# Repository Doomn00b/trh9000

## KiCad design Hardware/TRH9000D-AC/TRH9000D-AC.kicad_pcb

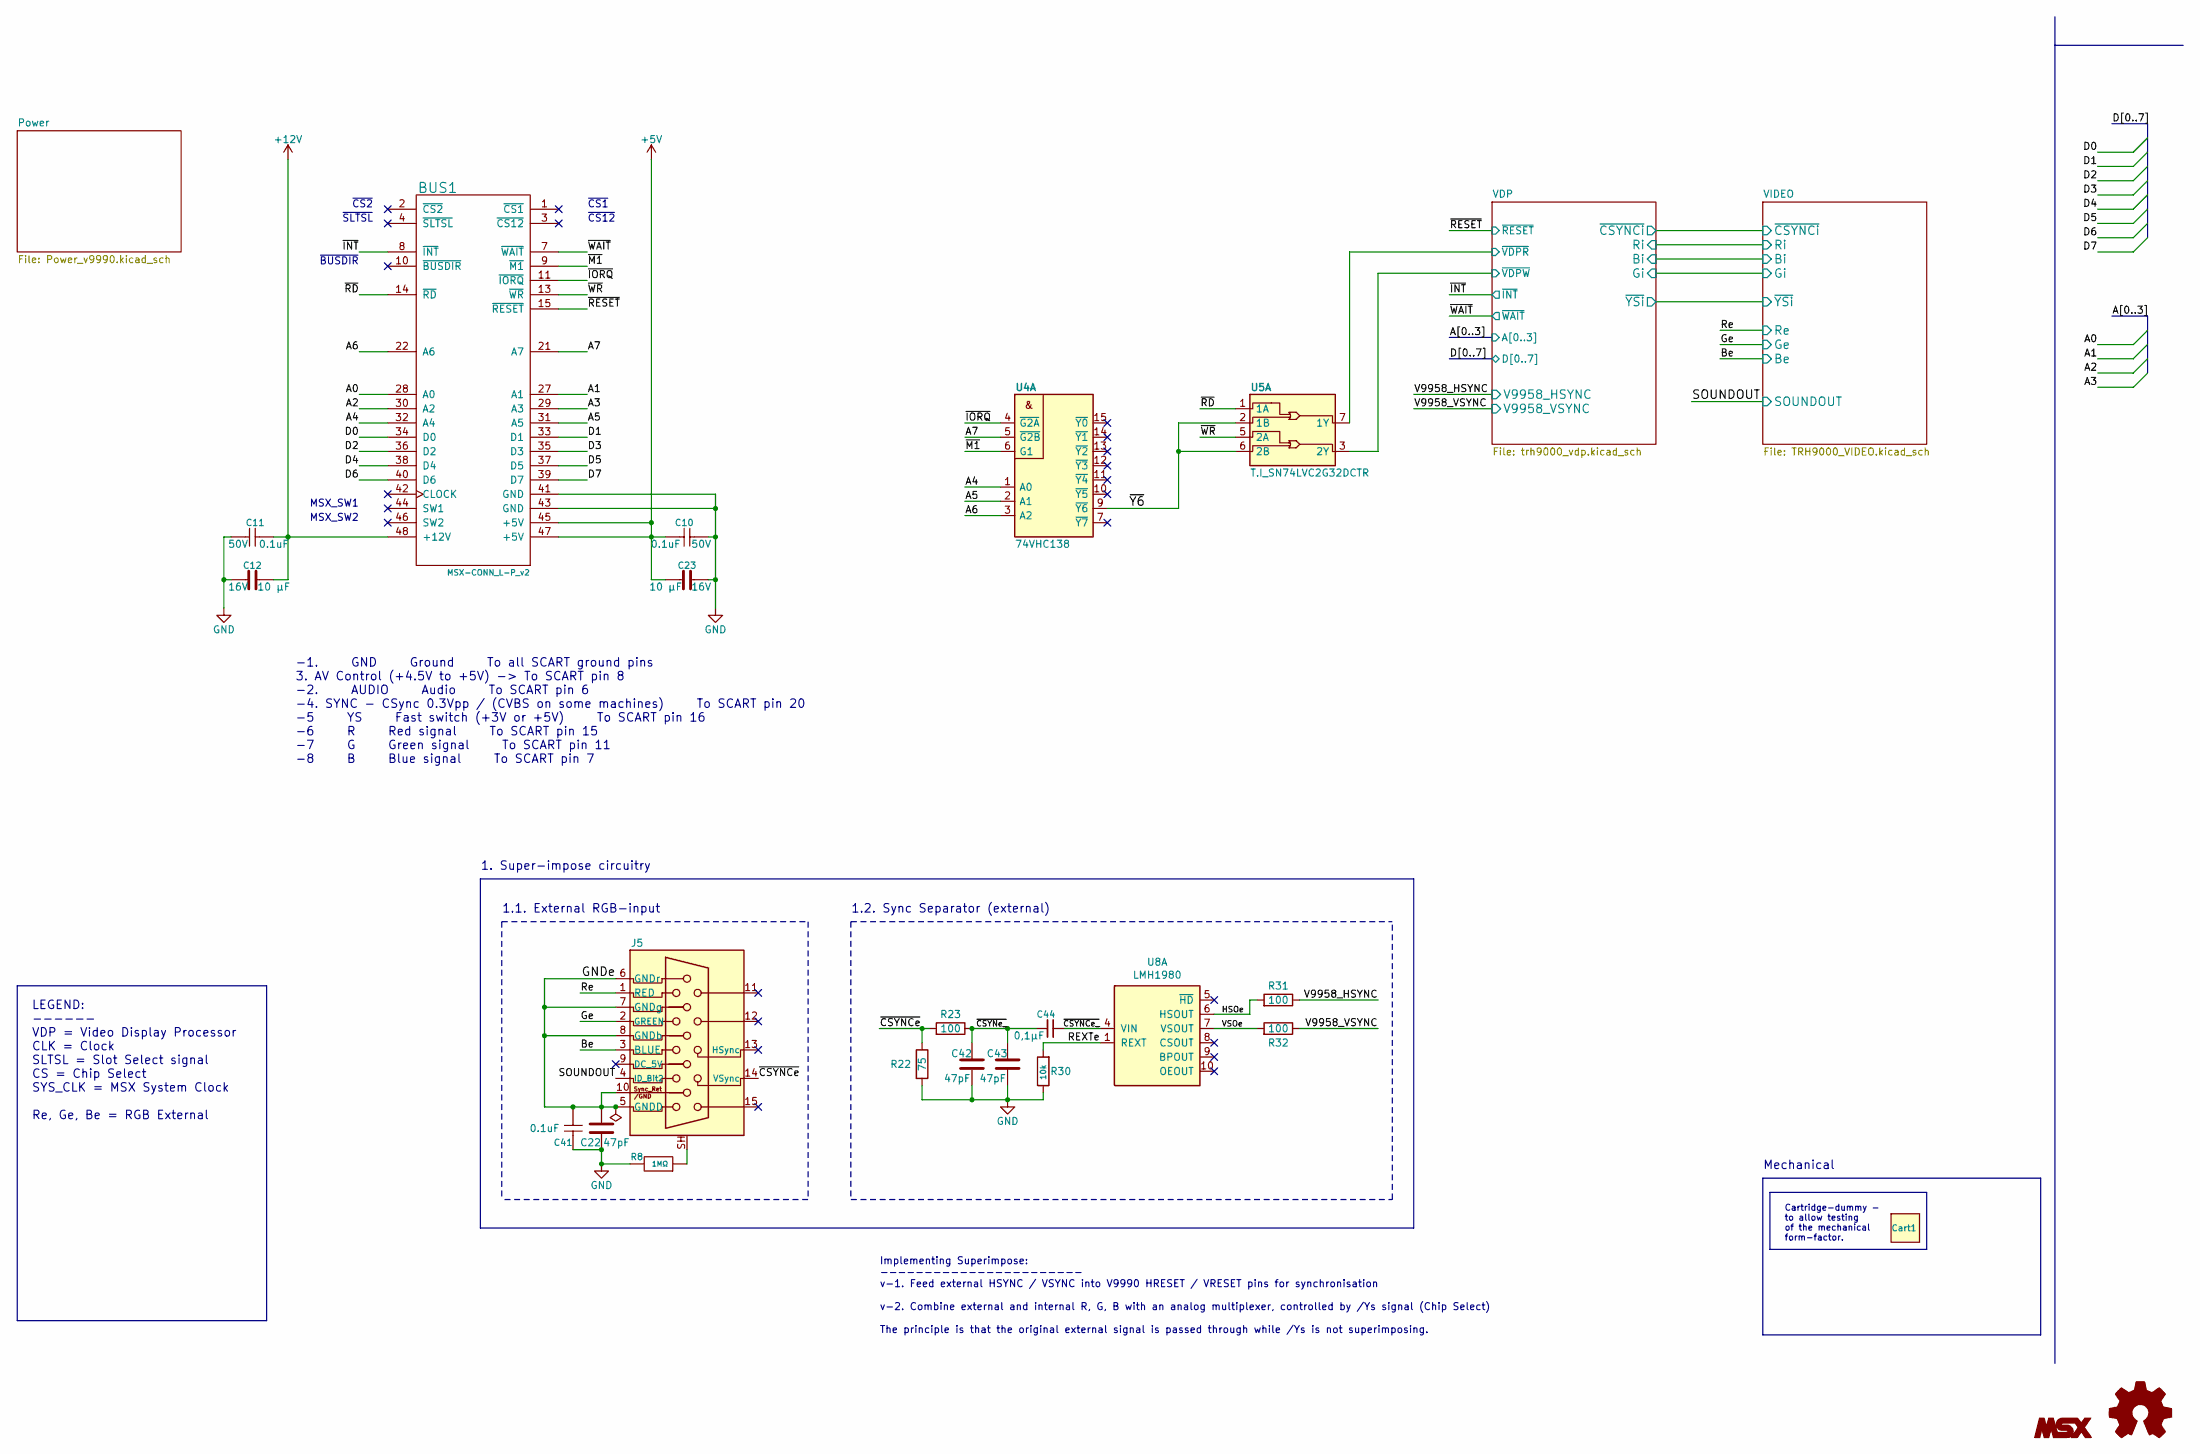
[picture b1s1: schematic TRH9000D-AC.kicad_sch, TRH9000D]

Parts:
BUS1: MSX-CONN_L-P_v2; msx_edge-conn-LP_v2; MPN n/a
C10, C11, C41: C_CC0805JPX7R9BB104; C_0805_2012Metric; Voltage rating 50V; MPN CC0805JPX7R9BB104
C12, C23: C_CL21B106KOQNNNE; C_0805_2012Metric; Voltage rating 16V; MPN CL21B106KOQNNNE
C22, C42: 47pF; C_0603_1608Metric
C43: 47pF; C_0603_1608Metric_round_court
C44: C_CL10B104KB8NNNL; C_0603_1608Metric_round_court; Tolerance ±10%; Voltage Rating 50V; MPN CL10B104KB8NNNL
Cart1: MSX-cartridge_dummy; MSX-cart-dummy_RA; MPN n/a
J5: Norcomp_200-015-263R001; Norcomp_DSUB-15-HD_Female_Horizontal_SMD_P0.77x1.98mm; Current Rating 2A; Voltage Rating 300V; MPN 200-015-263R001
LOGO1: Logo_Open_Hardware_Small; OSHW-Logo2_14.6x12mm_SilkScreen
LOGO2: Logo_MSX; Logo_MSX_10x3
R8: R_ERJ-3GEYJ105V; R_0603_1608Metric; Voltage rating 75V; MPN ERJ-3GEYJ105V
R22: 75; R_0603_1608Metric
R23: 100; R_0603_1608Metric_roundcourt
R30: R_RC0603FR-0710KL; R_0603_1608Metric_roundcourt; MPN RC0603FR-0710KL
R31, R32: 100; R_0603_1608Metric
U4: 74VHC138; SO-16_3.9x9.9mm_P1.27mm; MPN 74VHC138FT
U5: T.I_SN74LVC2G32DCTR; SSOP-8_2.95x2.8mm_P0.65mm; MPN SN74LVC2G32DCTR
U8: LMH1980; VSSOP-10_3x3mm_P0.5mm; MPN LMH1980MM/NOPBCT

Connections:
+5V: BUS1.45 (+5V), BUS1.47 (+5V), C10.1, C23.1; also elsewhere on the board
+12V: BUS1.48 (+12V), C11.1, C12.1; also elsewhere on the board
/A0: BUS1.28 (A0); also elsewhere on the board
/A1: BUS1.27 (A1); also elsewhere on the board
/A2: BUS1.30 (A2); also elsewhere on the board
/A3: BUS1.29 (A3); also elsewhere on the board
/A4: BUS1.32 (A4), U4.1 (A0)
/A5: BUS1.31 (A5), U4.2 (A1)
/A6: BUS1.22 (A6), U4.3 (A2)
/A7: BUS1.21 (A7), U4.5 (~G2B)
/Be: J5.3 (BLUE); also elsewhere on the board
/D0: BUS1.34 (D0); also elsewhere on the board
/D1: BUS1.33 (D1); also elsewhere on the board
/D2: BUS1.36 (D2); also elsewhere on the board
/D3: BUS1.35 (D3); also elsewhere on the board
/D4: BUS1.38 (D4); also elsewhere on the board
/D5: BUS1.37 (D5); also elsewhere on the board
/D6: BUS1.40 (D6); also elsewhere on the board
/D7: BUS1.39 (D7); also elsewhere on the board
/GNDe: C22.2, C41.2, J5.5 (GNDD), J5.6 (GNDr), J5.7 (GNDg), J5.8 (GNDb), J5.10 (Sync_Ret/GND)
/Ge: J5.2 (GREEN); also elsewhere on the board
/HSOe: R31.2, U8.6 (HSOUT)
/REXTe: R30.2, U8.1 (REXT)
/Re: J5.1 (RED); also elsewhere on the board
/SOUNDOUT: J5.4 (ID_Bit2); also elsewhere on the board
/V9958_HSYNC: R31.1; also elsewhere on the board
/V9958_VSYNC: R32.1; also elsewhere on the board
/VDP/~VDPR: U5.7 (1Y); also elsewhere on the board
/VDP/~VDPW: U5.3 (2Y); also elsewhere on the board
/VSOe: R32.2, U8.7 (VSOUT)
/~CSYNCe_: C44.1, U8.4 (VIN)
/~CSYNCe: J5.14 (VSync), R22.1, R23.2
/~CSYNe_: C42.1, C43.1, C44.2, R23.1
/~INT: BUS1.8 (~INT); also elsewhere on the board
/~IORQ: BUS1.11 (~IORQ), U4.4 (~G2A)
/~M1: BUS1.9 (~M1), U4.6 (G1)
/~RD: BUS1.14 (~RD), U5.1 (1A)
/~RESET: BUS1.15 (~RESET); also elsewhere on the board
/~WAIT: BUS1.7 (~WAIT); also elsewhere on the board
/~WR: BUS1.13 (~WR), U5.5 (2A)
/~Y6: U4.9 (~Y6), U5.2 (1B), U5.6 (2B)
GND: BUS1.41 (GND), BUS1.43 (GND), C10.2, C11.2, C12.2, C22.1, C23.2, C41.1, C42.2, C43.2, R8.2, R22.2, R30.1; also elsewhere on the board
unnamed: J5.SH, R8.1

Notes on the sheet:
1.1. External RGB-input
MSX_SW2
~{CS12}
~{BUSDIR}
Cartridge-dummy - to allow testing of the mechanical form-factor.
MSX_SW1
Mechanical
Implementing Superimpose: ----------------------- v-1. Feed external HSYNC / VSYNC into V9990 HRESET / VRESET pins for synchronisation v-2. Combine external and internal R, G, B with an analog multiplexer, controlled by /Ys signal (Chip Select) The principle is that the original external signal is 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
LEGEND: ------ VDP = Video Display Processor CLK = Clock SLTSL = Slot Select signal CS = Chip Select SYS_CLK = MSX System Clock Re, Ge, Be = RGB External
~{CS1}
~{CS2}
1. Super-impose circuitry
1.2. Sync Separator (external)
~{SLTSL}
-1. GND Ground To all SCART ground pins 3. AV Control (+4.5V to +5V) -> To SCART pin 8 -2. AUDIO Audio To SCART pin 6 -4. SYNC - CSync 0.3Vpp / (CVBS on some machines) To SCART pin 20 -5 YS Fast switch (+3V or +5V) To SCART pin 16 -6 R Red signal To SCART pin 15 -7 G Green signal To SCART pin 11 -8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

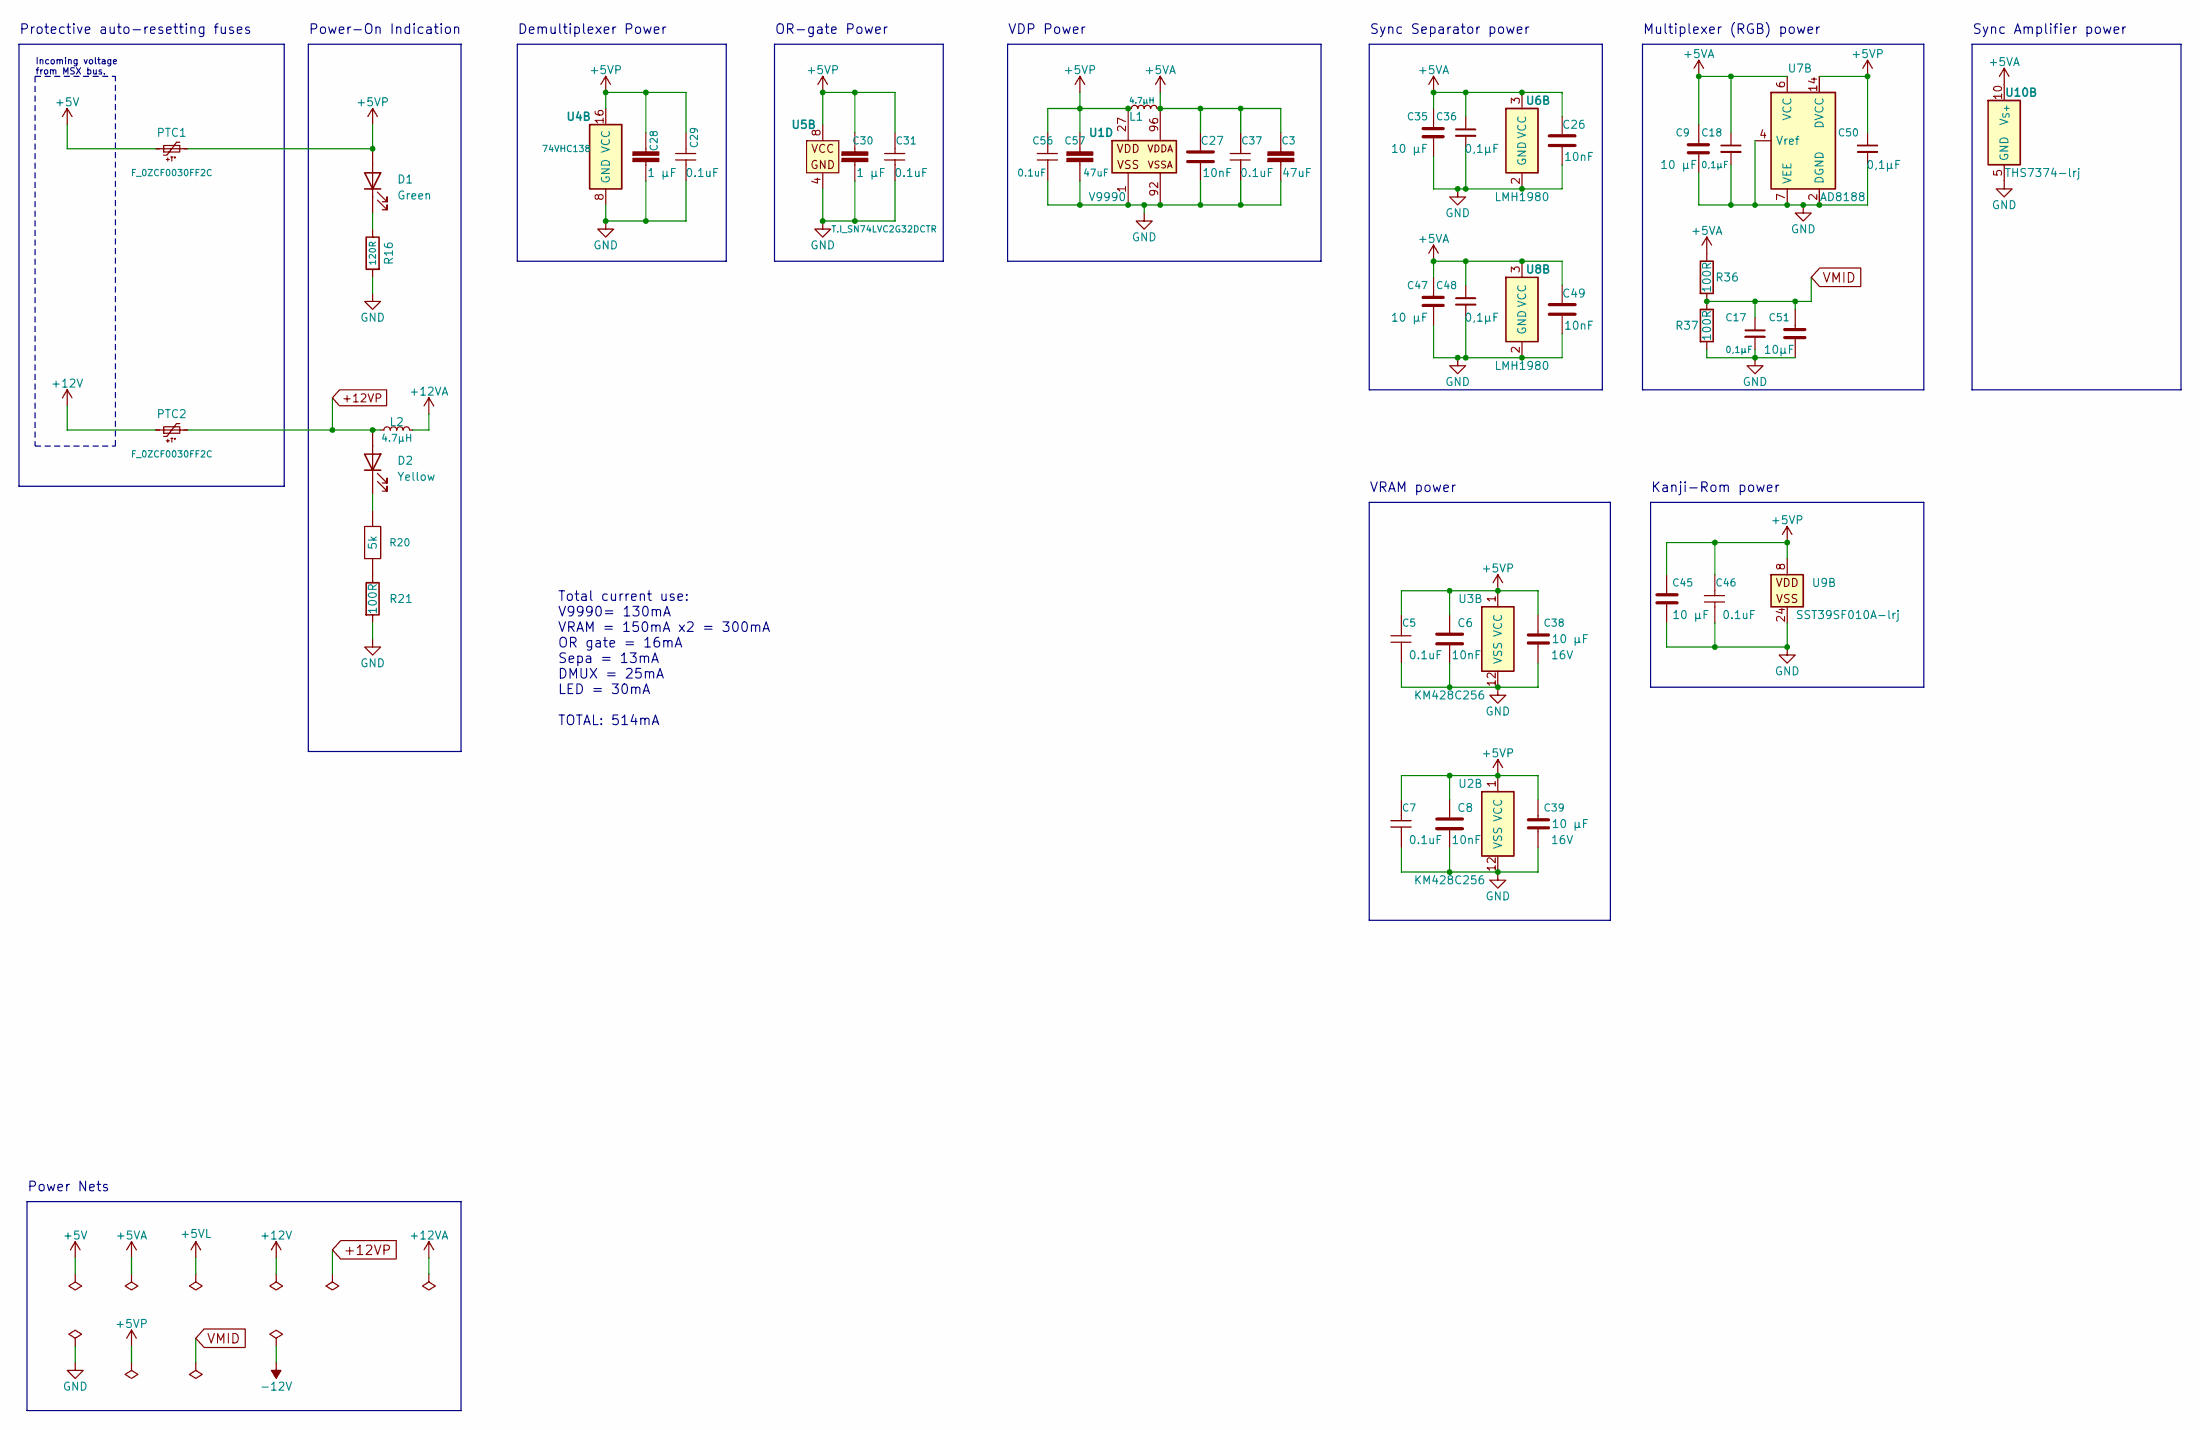
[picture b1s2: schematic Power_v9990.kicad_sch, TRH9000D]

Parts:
C3, C57: C_GRM21BR61A476ME15K; C_0805_2012Metric; Voltage rating 10V; Tolerance ±20%; MPN GRM21BR61A476ME15K
C5, C7, C29, C31, C37, C46, C56: C_CC0805JPX7R9BB104; C_0805_2012Metric; Voltage rating 50V; MPN CC0805JPX7R9BB104
C6, C8, C26, C27, C49: 10nF; C_0805_2012Metric
C9, C35, C38, C39, C45, C47, C51: C_CL21B106KOQNNNE; C_0805_2012Metric; Voltage rating 16V; MPN CL21B106KOQNNNE
C17, C18, C36, C48, C50: C_CL10B104KB8NNNL; C_0603_1608Metric_Pad1.08x0.95mm_HandSolder; Tolerance ±10%; Voltage Rating 50V; MPN CL10B104KB8NNNL
C28, C30: C_CL21B105KBFNNNF; C_0805_2012Metric_Pad1.18x1.45mm_HandSolder; Voltage rating 50V; MPN CL21B105KBFNNNF
D1: SunLED_XCVG12D; LED_D5.0mm; MPN XCVG12D
D2: LO_LED_LTL2R3K; LED_D5.0mm; MPN LTL2R3KYD-EM
L1, L2: L_MLZ2012M4R7HT000; L_0805_2012Metric; Current Rating 0.4A; MPN MLZ2012M4R7HT000
PTC1, PTC2: F_0ZCF0030FF2C; Fuse_2920_7451Metric; Voltage Rating 60V; Current Rating 100A; MPN 0ZCF0030FF2C
R16: 120R; R_0603_1608Metric
R20: R_RT0603BRE075KL; R_0603_1608Metric_Pad0.98x0.95mm_HandSolder; Tolerance ±0.1%; Voltage rating 75V; MPN MFR-25FBF52-10K
R21, R36, R37: 100R; R_0805_2012Metric
U1: V9990; LQFP-128_28x28mm_P0.8mm; MPN V9990
U2, U3: KM428C256; SOJ-40_400mil
U4: 74VHC138; SO-16_3.9x9.9mm_P1.27mm; MPN 74VHC138FT
U5: T.I_SN74LVC2G32DCTR; SSOP-8_2.95x2.8mm_P0.65mm; MPN SN74LVC2G32DCTR
U6, U8: LMH1980; VSSOP-10_3x3mm_P0.5mm; MPN LMH1980MM/NOPBCT
U7: AD8188; TSSOP-24_4.4x7.8mm_P0.65mm; MPN AD8188ARUZ
U9: SST39SF010A-lrj; TSOP-I-32_12.4x8mm_P0.5mm; Voltage Rating 5V; MPN SST39SF010A-70-4C-WHE
U10: THS7374-lrj; TSSOP-14_4.4x5mm_P0.65mm; MPN THS7374IPWR

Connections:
+5V: PTC1.1; also elsewhere on the board
+5VA: C3.1, C9.1, C18.1, C26.2, C27.2, C35.1, C36.1, C37.1, C47.1, C48.1, C49.2, L1.2, R36.1, U1.96 (VDDA), U6.3 (VCC), U7.6 (VCC), U7.13 (VCC), U7.17 (VCC), U7.21 (VCC), U7.24 (VCC), U8.3 (VCC), U10.10 (V_{S+}); also elsewhere on the board
+5VP: C5.1, C6.2, C7.1, C8.2, C28.1, C29.1, C30.1, C31.1, C38.1, C39.1, C45.1, C46.1, C50.1, C56.1, C57.1, D1.2 (A), L1.1, PTC1.2, U1.27 (VDD), U1.53 (VDD), U1.81 (VDD), U1.97 (VDD), U1.123 (VDD), U2.1 (VCC), U2.20 (VCC), U3.1 (VCC), U3.20 (VCC), U4.16 (VCC), U5.8 (VCC), U7.14 (DVCC), U9.8 (VDD); also elsewhere on the board
+12V: PTC2.1; also elsewhere on the board
+12VA: L2.2; also elsewhere on the board
+12VP: D2.2 (A), L2.1, PTC2.2
/A0: U1.4 (MODE0); also elsewhere on the board
/A1: U1.5 (MODE1); also elsewhere on the board
/A2: U1.6 (MODE2); also elsewhere on the board
/A3: U1.7 (MODE3); also elsewhere on the board
/D0: U1.114 (CD0); also elsewhere on the board
/D1: U1.115 (CD1); also elsewhere on the board
/D2: U1.116 (CD2); also elsewhere on the board
/D3: U1.117 (CD3); also elsewhere on the board
/D4: U1.119 (CD4); also elsewhere on the board
/D5: U1.120 (CD5); also elsewhere on the board
/D6: U1.121 (CD6); also elsewhere on the board
/D7: U1.122 (CD7); also elsewhere on the board
/V9958_HSYNC: U1.105 (~HRESET/CB4); also elsewhere on the board
/V9958_VSYNC: U1.106 (~VRESET/CB5); also elsewhere on the board
/VDP/B: U1.95 (B/D1/CB1); also elsewhere on the board
/VDP/G: U1.94 (G/D2/CB2); also elsewhere on the board
/VDP/KA9: U1.16 (KA9), U9.2 (A9)
/VDP/KA10: U1.15 (KA10), U9.31 (A10)
/VDP/KA11: U1.14 (KA11), U9.1 (A11)
/VDP/KA12: U1.13 (KA12), U9.12 (A12)
/VDP/KA13: U1.12 (KA13), U9.4 (A13)
/VDP/KA14: U1.11 (KA14), U9.5 (A14)
/VDP/KA15: U1.10 (KA15), U9.11 (A15)
/VDP/KA16: U1.9 (KA16), U9.10 (A16)
/VDP/MCKIN: U1.113 (MCKIN); also elsewhere on the board
/VDP/R: U1.93 (R/D3/CB3); also elsewhere on the board
/VDP/V0A0: U1.26 (V0_A0/KA0), U3.25 (A0), U9.20 (A0)
/VDP/V0A1: U1.25 (V0_A1/KA1), U3.24 (A1), U9.19 (A1)
/VDP/V0A2: U1.24 (V0_A2/KA2), U3.23 (A2), U9.18 (A2)
/VDP/V0A3: U1.23 (V0_A3/KA3), U3.22 (A3), U9.17 (A3)
/VDP/V0A4: U1.22 (V0_A4/KA4), U3.19 (A4), U9.16 (A4)
/VDP/V0A5: U1.21 (V0_A5/KA5), U3.18 (A5), U9.15 (A5)
/VDP/V0A6: U1.20 (V0_A6/KA6), U3.17 (A6), U9.14 (A6)
/VDP/V0A7: U1.19 (V0_A7/KA7), U3.16 (A7), U9.13 (A7)
/VDP/V0A8: U1.18 (V0_A8/KA8), U3.15 (A8), U9.3 (A8)
/VDP/V0D0: U1.36 (V0_D0/KD0), U3.8 (W0/DQ0), U9.21 (DQ0)
/VDP/V0D1: U1.35 (V0_D1/KD1), U3.9 (W1/DQ1), U9.22 (DQ1)
/VDP/V0D2: U1.34 (V0_D2/KD2), U3.10 (W2/DQ2), U9.23 (DQ2)
/VDP/V0D3: U1.33 (V0_D3/KD3), U3.11 (W3/DQ3), U9.25 (DQ3)
/VDP/V0D4: U1.31 (V0_D4/KD4), U3.31 (W4/DQ4), U9.26 (DQ4)
/VDP/V0D5: U1.30 (V0_D5/KD5), U3.32 (W5/DQ5), U9.27 (DQ5)
/VDP/V0D6: U1.29 (V0_D6/KD6), U3.33 (W6/DQ6), U9.28 (DQ6)
/VDP/V0D7: U1.28 (V0_D7/KD7), U3.34 (W7/DQ7), U9.29 (DQ7)
/VDP/V0S0: U1.52 (V0_S0), U3.3 (SDQ0)
/VDP/V0S1: U1.51 (V0_S1), U3.4 (SDQ1)
/VDP/V0S2: U1.50 (V0_S2), U3.5 (SDQ2)
/VDP/V0S3: U1.49 (V0_S3), U3.6 (SDQ3)
/VDP/V0S4: U1.48 (V0_S4), U3.36 (SDQ4)
/VDP/V0S5: U1.47 (V0_S5), U3.37 (SDQ5)
/VDP/V0S6: U1.46 (V0_S6), U3.38 (SDQ6)
/VDP/V0S7: U1.45 (V0_S7), U3.39 (SDQ7)
/VDP/V1A0: U1.80 (V1_A0), U2.25 (A0)
/VDP/V1A1: U1.79 (V1_A1), U2.24 (A1)
/VDP/V1A2: U1.78 (V1_A2), U2.23 (A2)
/VDP/V1A3: U1.77 (V1_A3), U2.22 (A3)
/VDP/V1A4: U1.76 (V1_A4), U2.19 (A4)
/VDP/V1A5: U1.74 (V1_A5), U2.18 (A5)
/VDP/V1A6: U1.73 (V1_A6), U2.17 (A6)
/VDP/V1A7: U1.72 (V1_A7), U2.16 (A7)
/VDP/V1A8: U1.71 (V1_A8), U2.15 (A8)
/VDP/V1D0: U1.82 (V1_D0), U2.8 (W0/DQ0)
/VDP/V1D1: U1.83 (V1_D1), U2.9 (W1/DQ1)
/VDP/V1D2: U1.84 (V1_D2), U2.10 (W2/DQ2)
/VDP/V1D3: U1.85 (V1_D3), U2.11 (W3/DQ3)
/VDP/V1D4: U1.87 (V1_D4), U2.31 (W4/DQ4)
/VDP/V1D5: U1.88 (V1_D5), U2.32 (W5/DQ5)
/VDP/V1D6: U1.89 (V1_D6), U2.33 (W6/DQ6)
/VDP/V1D7: U1.90 (V1_D7), U2.34 (W7/DQ7)
/VDP/V1S0: U1.61 (V1_S0), U2.3 (SDQ0)
/VDP/V1S1: U1.60 (V1_S1), U2.4 (SDQ1)
/VDP/V1S2: U1.59 (V1_S2), U2.5 (SDQ2)
/VDP/V1S3: U1.58 (V1_S3), U2.6 (SDQ3)
/VDP/V1S4: U1.57 (V1_S4), U2.36 (SDQ4)
/VDP/V1S5: U1.56 (V1_S5), U2.37 (SDQ5)
/VDP/V1S6: U1.55 (V1_S6), U2.38 (SDQ6)
/VDP/V1S7: U1.54 (V1_S7), U2.39 (SDQ7)
/VDP/VMREQ: U1.124 (~VMREQ); also elsewhere on the board
/VDP/Y+: U1.98 (XTAL1); also elsewhere on the board
/VDP/Y-: U1.99 (XTAL2); also elsewhere on the board
/VDP/~CSYNCi: U1.102 (~CSYNC/FLM); also elsewhere on the board
/VDP/~KOE: U1.37 (~KOE), U9.30 (~CE), U9.32 (~OE)
/VDP/~KWE: U9.7 (~WE); also elsewhere on the board
/VDP/~V0_CAS: U1.39 (~V0_CAS), U3.27 (~CAS)
/VDP/~V0_RAS: U1.38 (~V0_RAS), U3.14 (~RAS)
/VDP/~V0_SC: U1.42 (~V0_SC), U3.2 (SC)
/VDP/~V0_TR: U1.41 (~V0_TR/OE), U3.7 (~DT/~OE)
/VDP/~V0_WE: U1.40 (~V0_WE), U3.13 (R~WB/~WE)
/VDP/~V1_CAS: U1.63 (~V1_CAS), U2.27 (~CAS)
/VDP/~V1_RAS: U1.62 (~V1_RAS), U2.14 (~RAS)
/VDP/~V1_SC: U1.67 (V1_SC), U2.2 (SC)
/VDP/~V1_SOE: U1.68 (~V1_SOE), U2.35 (~SE)
/VDP/~V1_TR: U1.66 (~V1_TR/OE), U2.7 (~DT/~OE)
/VDP/~V1_WE: U1.65 (~V1_WE), U2.13 (R~WB/~WE)
/VDP/~VDPR: U1.2 (~CSW); also elsewhere on the board
/VDP/~VDPW: U1.3 (~CSR); also elsewhere on the board
/VDP/~VO_SOE: U1.43 (~V0_SOE), U3.35 (~SE)
/VDP/~YSi: U1.91 (~YS/D0/CB0); also elsewhere on the board
/~INT: U1.126 (~INT0), U1.127 (~INT1); also elsewhere on the board
/~RESET: U1.110 (~RESET); also elsewhere on the board
/~WAIT: U1.128 (~WAIT); also elsewhere on the board
GND: C3.2, C5.2, C6.1, C7.2, C8.1, C9.2, C17.2, C18.2, C26.1, C27.1, C28.2, C29.2, C30.2, C31.2, C35.2, C36.2, C37.2, C38.2, C39.2, C45.2, C46.2, C47.2, C48.2, C49.1, C50.2, C51.2, C56.2, C57.2, R16.2, R21.2, R37.2, U1.1 (VSS), U1.17 (VSS), U1.32 (VSS), U1.44 (VSS), U1.64 (VSS), U1.75 (VSS), U1.86 (VSS), U1.92 (VSSA), U1.100 (VSS), U1.107 (VSS), U1.118 (VSS), U2.12 (VSS), U2.21 (VSS), U2.29 (DSF), U2.30 (VSS), U2.40 (VSS), U3.12 (VSS), U3.21 (VSS), U3.29 (DSF), U3.30 (VSS), U3.40 (VSS), U4.8 (GND), U5.4 (GND), U6.2 (GND), U7.2 (DGND), U7.4 (Vref), U7.7 (VEE), U7.9 (VEE), U7.11 (VEE), U7.15 (VEE), U7.19 (VEE), U8.2 (GND), U9.24 (VSS), U10.5 (GND); also elsewhere on the board
unnamed: D1.1 (K), R16.1
unnamed: D2.1 (K), R20.2
unnamed: R20.1, R21.1
VMID: C17.1, C51.1, R36.2, R37.1; also elsewhere on the board

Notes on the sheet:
OR-gate Power
Total current use: V9990= 130mA VRAM = 150mA x2 = 300mA OR gate = 16mA Sepa = 13mA DMUX = 25mA LED = 30mA TOTAL: 514mA
Sync Separator power
Sync Amplifier power
Power Nets
Power-On Indication
VRAM power
Kanji-Rom power
Incoming voltage from MSX bus.
Multiplexer (RGB) power
Protective auto-resetting fuses
Demultiplexer Power
VDP Power

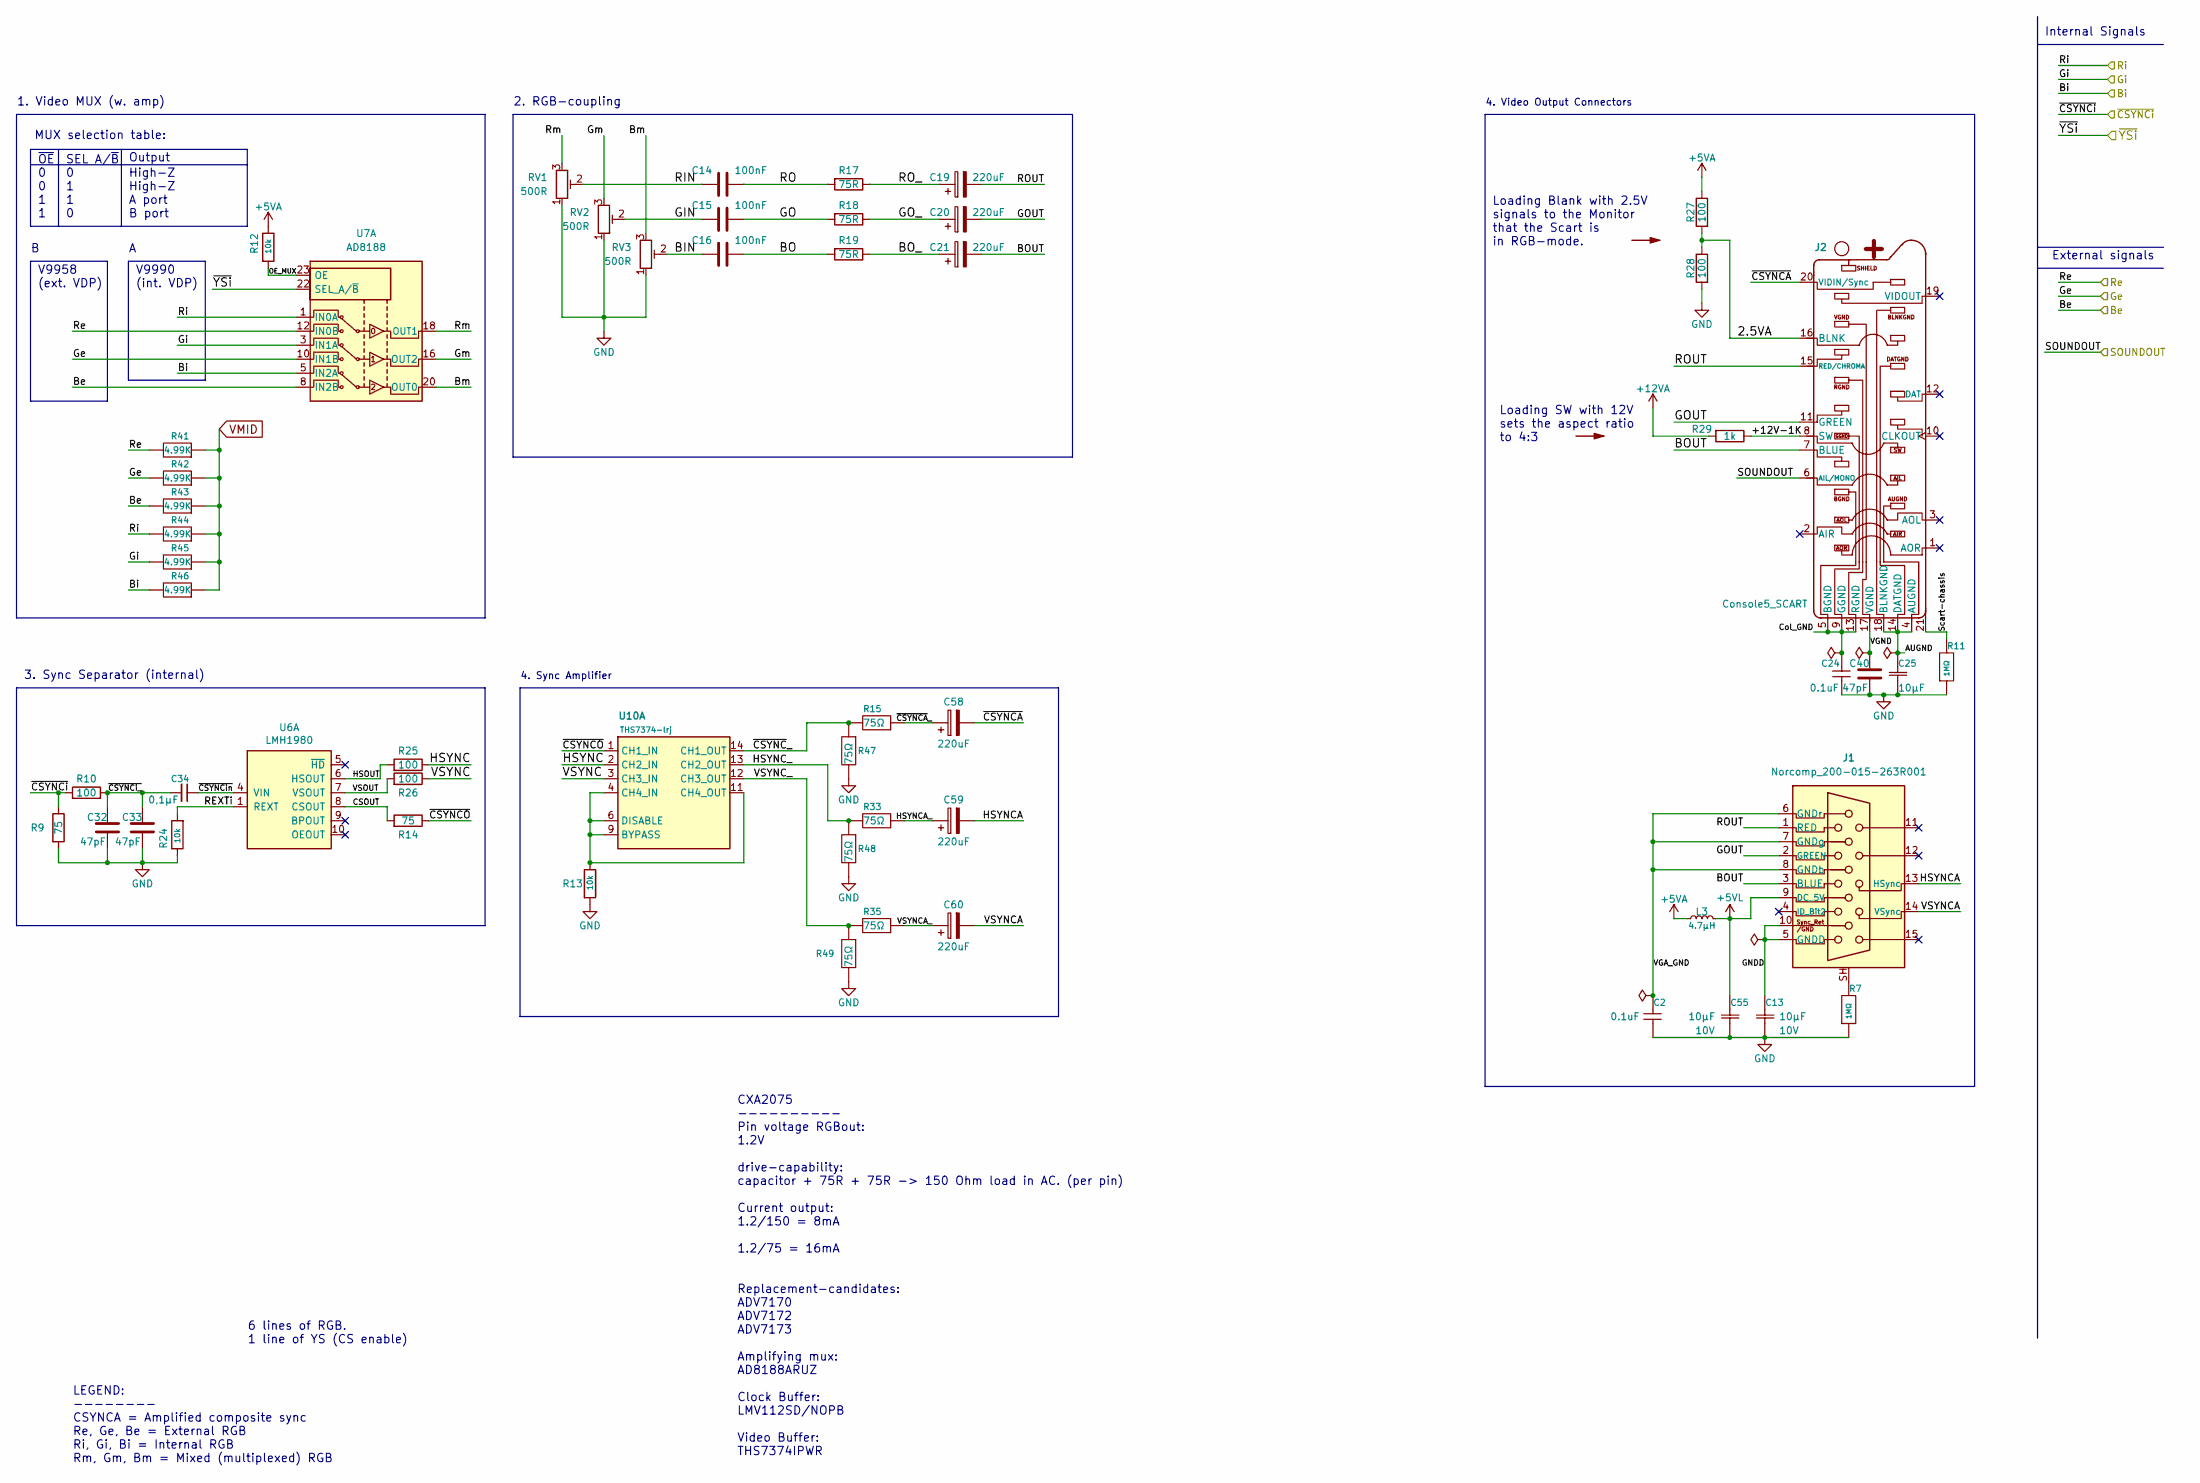
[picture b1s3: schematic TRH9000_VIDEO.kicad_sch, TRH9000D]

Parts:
C2: C_CC0805JPX7R9BB104; C_0805_2012Metric_round_court; Voltage rating 50V; MPN CC0805JPX7R9BB104
C13, C25, C55: C_GRM188D71A106KA73D; C_0603_1608Metric; Voltage rating 10V; MPN GRM188D71A106KA73D
C14, C15, C16: 100nF; C_0805_2012Metric
C19, C20, C21, C58, C59, C60: C_TCJB227; CP_EIA-3528-15_AVX-H; Voltage Rating 6.3V; MPN TCJB227M006R0070
C24: C_CC0805JPX7R9BB104; C_0805_2012Metric; Voltage rating 50V; MPN CC0805JPX7R9BB104
C32, C33, C40: 47pF; C_0603_1608Metric
C34: C_CL10B104KB8NNNL; C_0603_1608Metric_Pad1.08x0.95mm_HandSolder; Tolerance ±10%; Voltage Rating 50V; MPN CL10B104KB8NNNL
J1: Norcomp_200-015-263R001; Norcomp_DSUB-15-HD_Female_Horizontal_SMD_P0.77x1.98mm; Current Rating 2A; Voltage Rating 300V; MPN 200-015-263R001
J2: Console5_SCART; SCART-21_Female_Horizontal_P1.905x2.54mm_EdgePinOffset10.7m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; MPN N/A
L3: L_MLZ2012M4R7HT000; L_0805_2012Metric; Current Rating 0.4A; MPN MLZ2012M4R7HT000
R7, R11: R_ERJ-3GEYJ105V; R_0603_1608Metric; Voltage rating 75V; MPN ERJ-3GEYJ105V
R9, R14: 75; R_0603_1608Metric
R10, R25, R26, R27, R28: 100; R_0603_1608Metric
R12, R13, R24: R_RC0603FR-0710KL; R_0603_1608Metric_roundcourt; MPN RC0603FR-0710KL
R15, R33, R35, R47, R48, R49: R_ERJ-PA3F75R0V; R_0603_1608Metric_roundcourt; Voltage rating 49V; MPN ERJ-PA3F75R0V
R17, R18, R19: 75R; R_0805_2012Metric
R29: 1k; R_0603_1608Metric
R41, R42, R43, R44, R45, R46: R_CRCW08054K99FKEAHP; R_0805_2012Metric_Pad1.20x1.40mm_HandSolder; MPN CRCW08054K99FKEAHP
RV1, RV2, RV3: 500R; Potentiometer_Bourns_3314G_Vertical_lrj
U6: LMH1980; VSSOP-10_3x3mm_P0.5mm; MPN LMH1980MM/NOPBCT
U7: AD8188; TSSOP-24_4.4x7.8mm_P0.65mm; MPN AD8188ARUZ
U10: THS7374-lrj; TSSOP-14_4.4x5mm_P0.65mm; MPN THS7374IPWR

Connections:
+5VA: L3.1, R12.1, R27.1; also elsewhere on the board
+5VL: C55.2, J1.9 (DC_5V), L3.2
+12VA: R29.2; also elsewhere on the board
/Be: R43.2, U7.8 (IN2B); also elsewhere on the board
/Ge: R42.2, U7.10 (IN1B); also elsewhere on the board
/Re: R41.2, U7.12 (IN0B); also elsewhere on the board
/SOUNDOUT: J2.6 (AIL/MONO); also elsewhere on the board
/VDP/Bi: R46.2, U7.5 (IN2A); also elsewhere on the board
/VDP/Gi: R45.2, U7.3 (IN1A); also elsewhere on the board
/VDP/Ri: R44.2, U7.1 (IN0A); also elsewhere on the board
/VDP/~CSYNCi: R9.1, R10.2; also elsewhere on the board
/VDP/~YSi: U7.22 (SEL_A/~B); also elsewhere on the board
/VIDEO/2.5VA: J2.16 (BLNK), R27.2, R28.1
/VIDEO/+12V-1K: J2.8 (SW), R29.1
/VIDEO/AUGND: C25.2, J2.4 (AUGND), J2.14 (DATGND), J2.18 (BLNKGND)
/VIDEO/BIN: C16.2, RV3.2
/VIDEO/BO: C16.1, R19.2
/VIDEO/BOUT: C21.2, J1.3 (BLUE), J2.7 (BLUE)
/VIDEO/BO_: C21.1, R19.1
/VIDEO/Bm: RV3.3, U7.20 (OUT0)
/VIDEO/CSOUT: R14.2, U6.8 (CSOUT)
/VIDEO/Col_GND: C24.1, J2.5 (BGND), J2.9 (GGND), J2.13 (RGND)
/VIDEO/GIN: C15.2, RV2.2
/VIDEO/GNDD: C13.2, J1.5 (GNDD), J1.10 (Sync_Ret/GND)
/VIDEO/GO: C15.1, R18.2
/VIDEO/GOUT: C20.2, J1.2 (GREEN), J2.11 (GREEN)
/VIDEO/GO_: C20.1, R18.1
/VIDEO/Gm: RV2.3, U7.16 (OUT2)
/VIDEO/HSOUT: R25.2, U6.6 (HSOUT)
/VIDEO/HSYNC: R25.1, U10.2 (CH2_IN)
/VIDEO/HSYNCA: C59.2, J1.13 (HSync)
/VIDEO/HSYNCA_: C59.1, R33.1
/VIDEO/HSYNC_: R33.2, R48.1, U10.13 (CH2_OUT)
/VIDEO/OE_MUX: R12.2, U7.23 (OE)
/VIDEO/REXTi: R24.2, U6.1 (REXT)
/VIDEO/RIN: C14.2, RV1.2
/VIDEO/RO: C14.1, R17.2
/VIDEO/ROUT: C19.2, J1.1 (RED), J2.15 (RED/CHROMA)
/VIDEO/RO_: C19.1, R17.1
/VIDEO/Rm: RV1.3, U7.18 (OUT1)
/VIDEO/Scart-chassis: J2.21 (SH), R11.2
/VIDEO/VGA_GND: C2.1, J1.6 (GNDr), J1.7 (GNDg), J1.8 (GNDb)
/VIDEO/VGND: C40.1, J2.17 (VGND)
/VIDEO/VSOUT: R26.2, U6.7 (VSOUT)
/VIDEO/VSYNC: R26.1, U10.3 (CH3_IN)
/VIDEO/VSYNCA: C60.2, J1.14 (VSync)
/VIDEO/VSYNCA_: C60.1, R35.1
/VIDEO/VSYNC_: R35.2, R49.1, U10.12 (CH3_OUT)
/VIDEO/~CSYNCA: C58.2, J2.20 (VIDIN/Sync)
/VIDEO/~CSYNCA_: C58.1, R15.1
/VIDEO/~CSYNCO: R14.1, U10.1 (CH1_IN)
/VIDEO/~CSYNCi_: C32.1, C33.1, C34.2, R10.1
/VIDEO/~CSYNCin: C34.1, U6.4 (VIN)
/VIDEO/~CSYNC_: R15.2, R47.1, U10.14 (CH1_OUT)
GND: C2.2, C13.1, C24.2, C25.1, C32.2, C33.2, C40.2, C55.1, R7.1, R9.2, R11.1, R13.2, R24.1, R28.2, R47.2, R48.2, R49.2, RV1.1, RV2.1, RV3.1; also elsewhere on the board
unnamed: J1.SH, R7.2
unnamed: R13.1, U10.4 (CH4_IN), U10.6 (DISABLE), U10.9 (BYPASS), U10.11 (CH4_OUT)
VMID: R41.1, R42.1, R43.1, R44.1, R45.1, R46.1; also elsewhere on the board

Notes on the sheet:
Internal Signals
CXA2075 ---------- Pin voltage RGBout: 1.2V drive-capability: capacitor + 75R + 75R -> 150 Ohm load in AC. (per pin) Current output: 1.2/150 = 8mA 1.2/75 = 16mA Replacement-candidates: ADV7170 ADV7172 ADV7173 Amplifying mux: AD8188ARUZ Clock Buffer: LMV112SD/NOPB Video Buffer: THS7374IPWR
3. Sync Separator (internal)
4. Sync Amplifier
Loading Blank with 2.5V signals to the Monitor that the Scart is in RGB-mode.
Output
V9990 (int. VDP)
~{OE} 0 0 1 1
LEGEND: -------- CSYNCA = Amplified composite sync Re, Ge, Be = External RGB Ri, Gi, Bi = Internal RGB Rm, Gm, Bm = Mixed (multiplexed) RGB
High-Z High-Z A port B port
1. Video MUX (w. amp)
4. Video Output Connectors
External signals
2. RGB-coupling
SEL A/~{B} 0 1 1 0
MUX selection table:
6 lines of RGB. 1 line of YS (CS enable)
Loading SW with 12V sets the aspect ratio to 4:3
V9958 (ext. VDP)

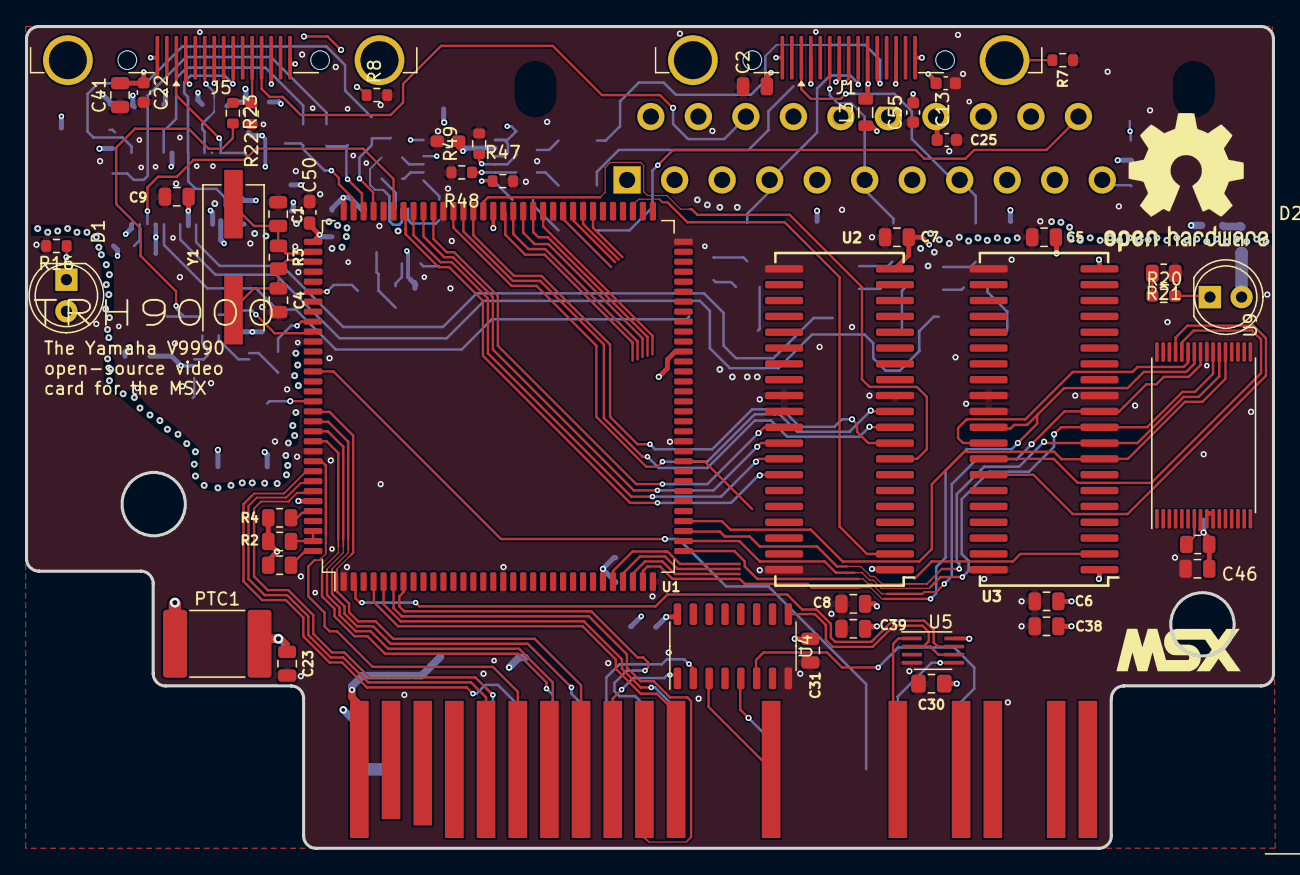
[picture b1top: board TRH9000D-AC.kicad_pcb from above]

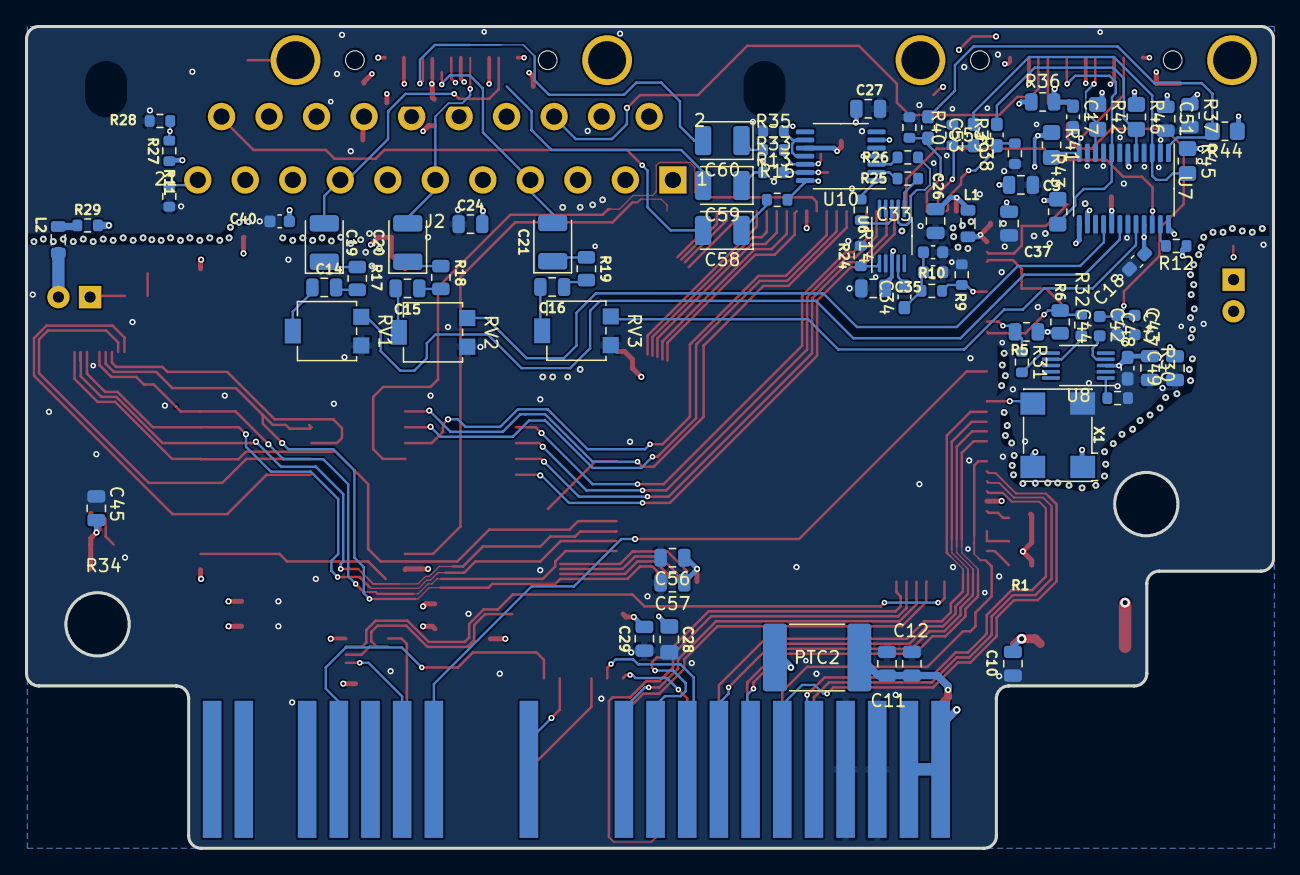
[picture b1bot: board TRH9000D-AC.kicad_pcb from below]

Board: 4 copper layers, 100.0 x 65.9 mm, 138 parts (85 on the bottom side), 180 nets.

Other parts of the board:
C1, C4: 27pF; C_0805_2012Metric
C52, C53, C54: C_CL10B104KB8NNNL; C_0603_1608Metric_Pad1.08x0.95mm_HandSolder
R1, R2, R4, R5, R6, R34: 4K7; R_0805_2012Metric
R3: 10M; R_0805_2012Metric
R38, R39, R40: R_ERJ-PA3F75R0V; R_0603_1608Metric_roundcourt
X1: Crystek_CE3291; Oscillator_SMD_Abracon_ASV-4Pin_7.0x5.1mm
Y1: Y_HCM4921477270ABJT; Crystal_HC49-US_Vertical_cy_mod

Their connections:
+5VA: R5.1, R6.2, X1.1 (E/D), X1.4 (Vcc); also elsewhere on the board
+5VP: R1.1, R2.1, R4.1, R34.1; also elsewhere on the board
/V9958_HSYNC: R5.2; also elsewhere on the board
/V9958_VSYNC: R6.1; also elsewhere on the board
/VDP/B: C54.1, R38.2; also elsewhere on the board
/VDP/Bi: C54.2; also elsewhere on the board
/VDP/G: C53.1, R39.2; also elsewhere on the board
/VDP/Gi: C53.2; also elsewhere on the board
/VDP/MCKIN: X1.3 (OUT); also elsewhere on the board
/VDP/R: C52.1, R40.2; also elsewhere on the board
/VDP/Ri: C52.2; also elsewhere on the board
/VDP/VMREQ: R4.2; also elsewhere on the board
/VDP/Y+: C1.1, R3.2, Y1.1; also elsewhere on the board
/VDP/Y-: C4.1, R3.1, Y1.2; also elsewhere on the board
/VDP/~KWE: R34.2; also elsewhere on the board
/~INT: R2.2; also elsewhere on the board
/~WAIT: R1.2; also elsewhere on the board
GND: C1.2, C4.2, R38.1, R39.1, R40.1, X1.2 (GND); also elsewhere on the board

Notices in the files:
Hardware/Kicad/TRH9000/Power_v9990.kicad_sch:
Shared under CERN-OHL-S license
